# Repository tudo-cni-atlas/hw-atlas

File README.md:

hw-altas
================
## Firmware 

The firmware for STM32-based ATLAS anchor and tag nodes is provided as .elf file. 

## Hardware design
A minimal node PCB for the DecaWave DWM1000 module and the STM32F103C8T6 Evaluation Board known as "Blue Pill".

### Project schematic:

### BOM
| Identifier | Type/Value | Quantity | Supplier Id | Supplier | Comment |
| ---        | ---        | ---      | ---         | ---      | ---     |
| R1-R7 | 10 kΩ | 7 | RND 0805 1 1,0K | [Reichelt][reichelt] |
| C7 | 470 pF | 1 | NPO-G0805 470P | [Reichelt][reichelt] |
| C5, C6 | 10 µF | 2 | RND 1500805X1062 | [Reichelt][reichelt] |
| C1-C4 | 22 µF | 4 | X5R 0805 DB 22U | [Reichelt][reichelt] |
| LED_SYS | LED white | 1 | SLO SMD-W0805-0 | [Reichelt][reichelt] |
| LED_ERR | LED red | 1 | OSO LHR974 | [Reichelt][reichelt] |
| LED_SYS | LED white | 1 | SLO SMD-W0805-0 | [Reichelt][reichelt] |
| LED_TX | LED red | 1 | OSO LHR974 | [Reichelt][reichelt] |
| LED_RX | LED green | 1 | OSO LGR971 | [Reichelt][reichelt] |
| LED_SFD | LED yellow | 1 | RND 135-00051 | [Reichelt][reichelt] |
| LED_OK | LED green | 1 | OSO LGR971 | [Reichelt][reichelt] |
| IC1 | DWM1000 | 1 | 1479-1002-1-ND | [Digikey][digikey] |
| IC2 | MIC5219-3.3 | 1 | - | [Aliexpress][aliexpress] |
| BOARD1 | STM32 Eval Board | 1 | - | [Aliexpress][aliexpress] |

[reichelt]: http://www.reichelt.de
[mouser]: http://mouser.com
[aliexpress]: http://www.aliexpress.com
[digikey]: http://www.digikey.de

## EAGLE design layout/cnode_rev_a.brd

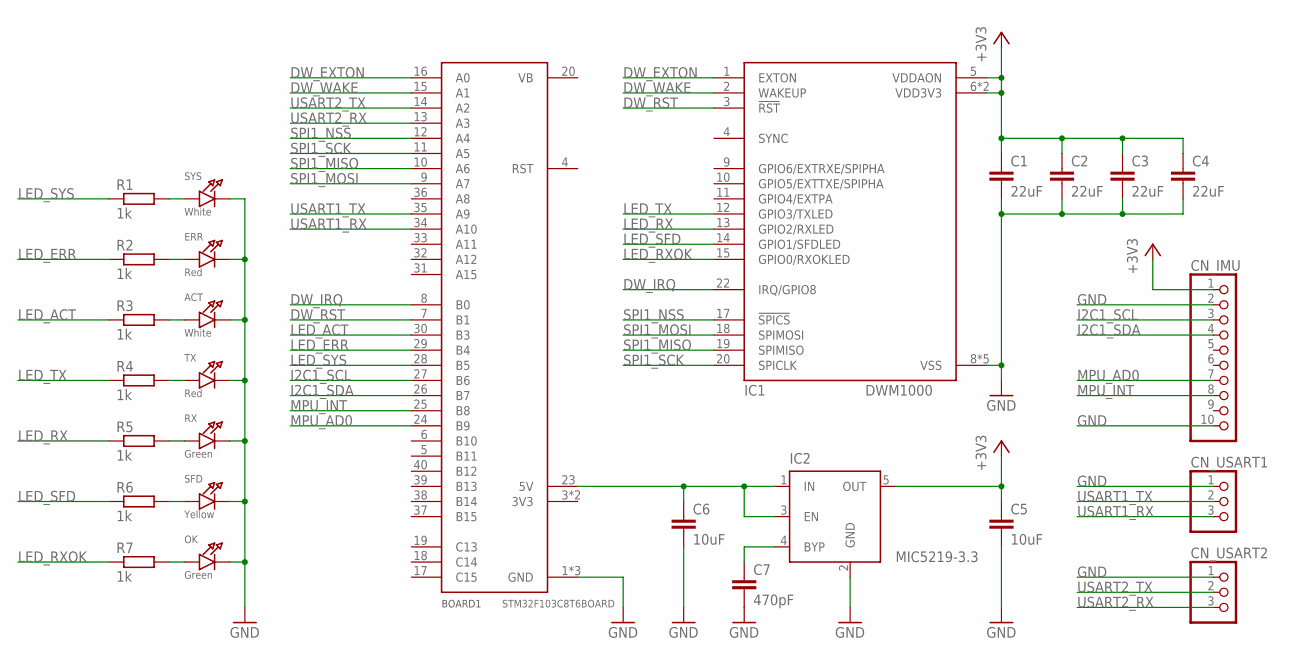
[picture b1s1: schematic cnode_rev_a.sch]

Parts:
ACT: White; CHIPLED_0805_NOOUTLINE
BOARD1: STM32F103C8T6BOARD
C1, C2, C3, C4: 22uF; C0805
C5, C6: 10uF; C0805
C7: 470pF; C0805
CN_IMU: HEADER-1X10ROUND; 1X10_ROUND
CN_USART1, CN_USART2: HEADER-1X3ROUND; 1X03_ROUND
ERR: Red; CHIPLED_0805_NOOUTLINE
IC1: DWM1000
IC2: MIC5219-3.3; SOT23-5
OK: Green; CHIPLED_0805_NOOUTLINE
R1, R2, R3, R4, R5, R6, R7: 1k; R0805
RX: Green; CHIPLED_0805_NOOUTLINE
SFD: Yellow; CHIPLED_0805_NOOUTLINE
SYS: White; CHIPLED_0805_NOOUTLINE
TX: Red; CHIPLED_0805_NOOUTLINE

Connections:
+3V3: C1.1, C2.1, C3.1, C4.1, C5.1, CN_IMU.1, IC1.5 (VDDAON), IC1.6 (VDD3V3), IC1.7 (VDD3V3), IC2.5 (OUT)
DW_EXTON: BOARD1.16 (A0), IC1.1 (EXTON)
DW_IRQ: BOARD1.8 (B0), IC1.22 (IRQ/GPIO8)
DW_RST: BOARD1.7 (B1), IC1.3 (!RST)
DW_WAKE: BOARD1.15 (A1), IC1.2 (WAKEUP)
GND: ACT.C, BOARD1.1 (GND), BOARD1.2 (GND), BOARD1.22 (GND), C1.2, C2.2, C3.2, C4.2, C5.2, C6.2, C7.2, CN_IMU.2, CN_IMU.10, CN_USART1.1, CN_USART2.1, ERR.C, IC1.8 (VSS), IC1.16 (VSS), IC1.21 (VSS), IC1.23 (VSS), IC1.24 (VSS), IC2.2 (GND), OK.C, RX.C, SFD.C, SYS.C, TX.C
I2C1_SCL: BOARD1.27 (B6), CN_IMU.3
I2C1_SDA: BOARD1.26 (B7), CN_IMU.4
LED_ACT: BOARD1.30 (B3), R3.1
LED_ERR: BOARD1.29 (B4), R2.1
LED_RX: IC1.13 (GPIO2/RXLED), R5.1
LED_RXOK: IC1.15 (GPIO0/RXOKLED), R7.1
LED_SFD: IC1.14 (GPIO1/SFDLED), R6.1
LED_SYS: BOARD1.28 (B5), R1.1
LED_TX: IC1.12 (GPIO3/TXLED), R4.1
MPU_AD0: BOARD1.24 (B9), CN_IMU.7
MPU_INT: BOARD1.25 (B8), CN_IMU.8
unnamed: R5.2, RX.A
unnamed: R4.2, TX.A
unnamed: ACT.A, R3.2
unnamed: ERR.A, R2.2
unnamed: R1.2, SYS.A
unnamed: BOARD1.23 (5V), C6.1, IC2.1 (IN), IC2.3 (EN)
unnamed: C7.1, IC2.4 (BYP)
unnamed: R6.2, SFD.A
unnamed: OK.A, R7.2
SPI1_MISO: BOARD1.10 (A6), IC1.19 (SPIMISO)
SPI1_MOSI: BOARD1.9 (A7), IC1.18 (SPIMOSI)
SPI1_NSS: BOARD1.12 (A4), IC1.17 (!SPICS)
SPI1_SCK: BOARD1.11 (A5), IC1.20 (SPICLK)
USART1_RX: BOARD1.34 (A10), CN_USART1.3
USART1_TX: BOARD1.35 (A9), CN_USART1.2
USART2_RX: BOARD1.13 (A3), CN_USART2.3
USART2_TX: BOARD1.14 (A2), CN_USART2.2

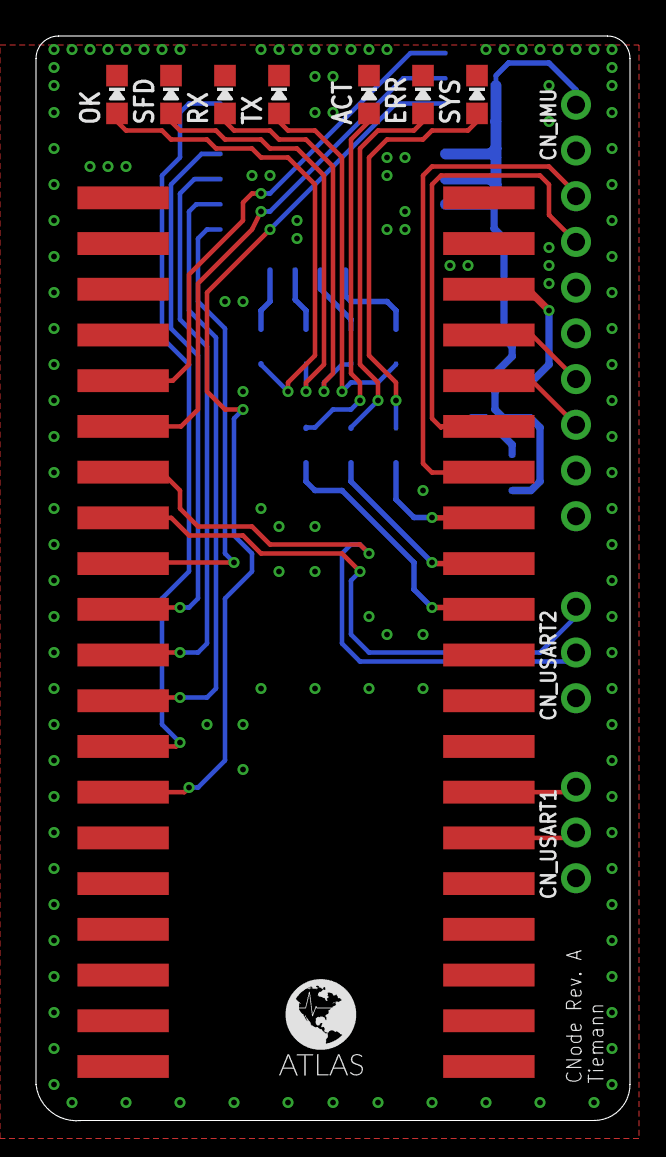
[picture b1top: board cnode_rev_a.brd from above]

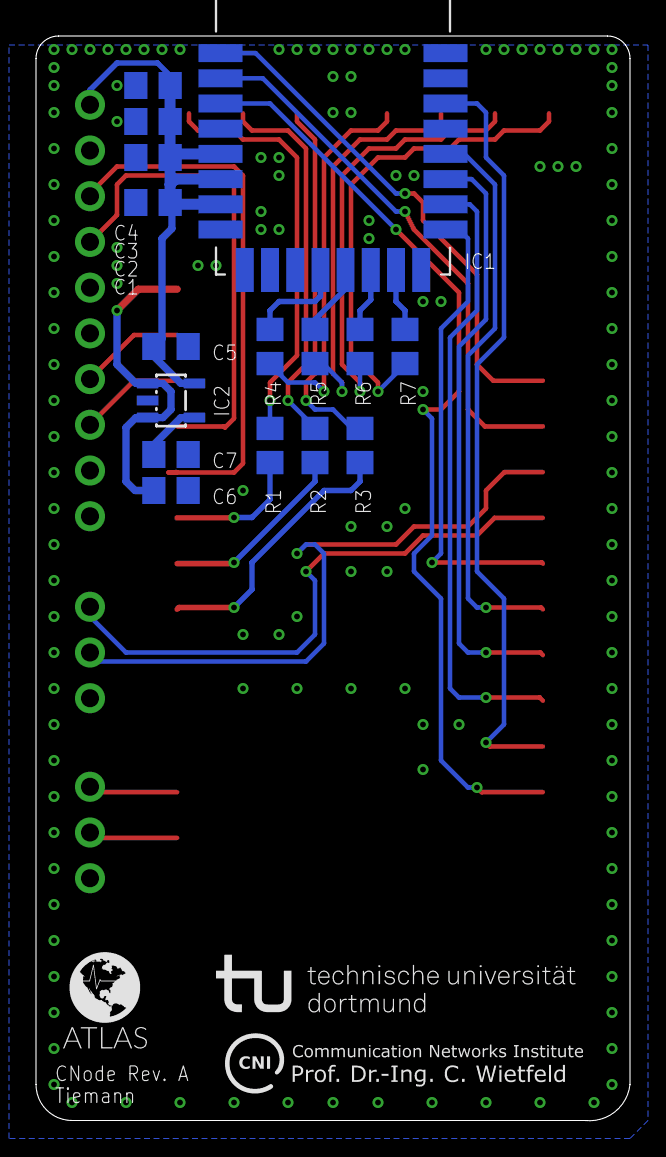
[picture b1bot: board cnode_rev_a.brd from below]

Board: 2 copper layers, 33.0 x 60.3 mm, 31 parts (19 on the bottom side), 34 nets.

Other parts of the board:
U$2, U$4: ATLAS_LOGO_5MM
U$5: CNI-BANNER-EN_20MM
U$6: TU-BANNER_20MM

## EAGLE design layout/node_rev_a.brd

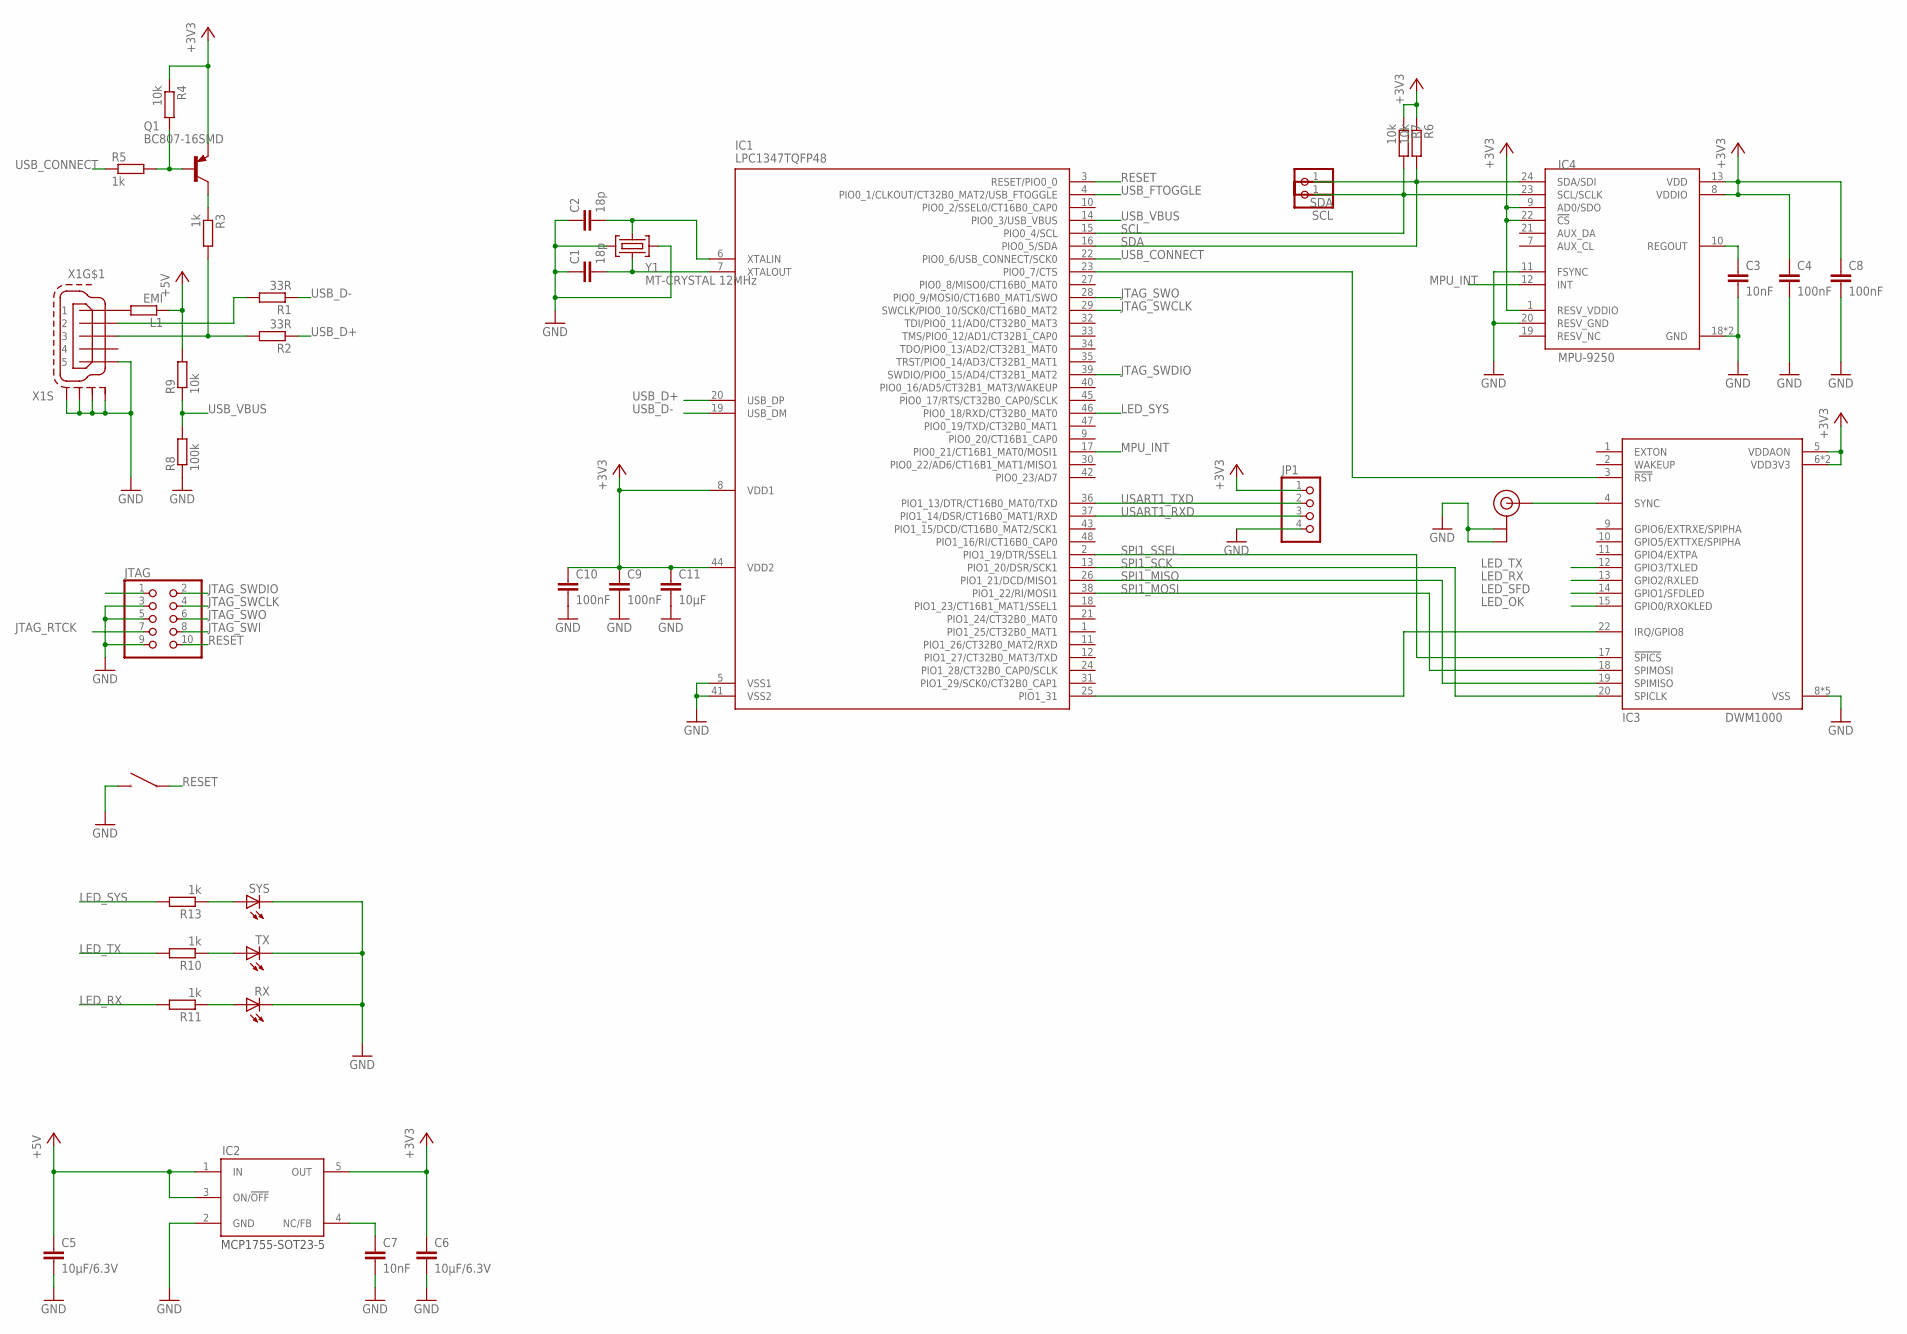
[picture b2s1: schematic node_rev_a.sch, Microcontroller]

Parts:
C1, C2: 18p; C0603
C3, C7: 10nF; C0603
C4, C8, C9, C10: 100nF; C0603
C5, C6: 10µF/6.3V; C0603
C11: 10µF; C0603
IC1: LPC1347TQFP48; LQFP48-7X7
IC2: MCP1755-SOT23-5; SOT23-5
IC3: DWM1000
IC4: MPU-9250; QFN24_3MM
JP1: HEADER-1X4ROUND; 1X04_ROUND
JTAG: ARM-JTAG_1.27-SMD; 20021121-10010XXLF
L1: EMI; R0603
Q1: BC807-16SMD; SOT23-BEC
R1, R2: 33R; R0603
R3, R5, R10, R11, R13: 1k; R0603
R4, R6, R7, R9: 10k; R0603
R8: 100k; R0603
RX: LEDCHIP-LED0603; CHIP-LED0603
SCL: HEADER-1X12MM; 1X01_2MM
SDA: HEADER-1X12MM; 1X01_2MM
SYNC: U.FL
SYS: LEDCHIP-LED0603; CHIP-LED0603
TX: LEDCHIP-LED0603; CHIP-LED0603
U$1: TACT-SWITCH-40-40; 40-40
X1: MINI-USB-SCHIELD-32005-201; 32005-201
Y1: MT-CRYSTAL 12MHz; MT

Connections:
+3V3: C4.1, C6.1, C8.1, C9.1, C10.1, C11.1, IC1.8 (VDD1), IC1.44 (VDD2), IC2.5 (OUT), IC3.5 (VDDAON), IC3.6 (VDD3V3), IC3.7 (VDD3V3), IC4.1 (RESV_VDDIO), IC4.8 (VDDIO), IC4.9 (AD0/SDO), IC4.13 (VDD), IC4.22 (!CS), JP1.1, Q1.E, R4.1, R6.1, R7.1
+5V: C5.1, IC2.1 (IN), IC2.3 (ON/!OFF), L1.1, R9.2
GND: C1.1, C2.1, C3.2, C4.2, C5.2, C6.2, C7.2, C8.2, C9.2, C10.2, C11.2, IC1.5 (VSS1), IC1.41 (VSS2), IC2.2 (GND), IC3.8 (VSS), IC3.16 (VSS), IC3.21 (VSS), IC3.23 (VSS), IC3.24 (VSS), IC4.11 (FSYNC), IC4.18 (GND), IC4.20 (RESV_GND), IC4.THERM (GND), JP1.4, JTAG.3, JTAG.5, JTAG.9, R8.1, RX.C, SYNC.1 (GND), SYNC.2 (GND), SYS.C, TX.C, U$1.1, U$1.2, X1.5, X1.M1 (S1), X1.M2 (S2), X1.M3 (S3), X1.M4 (S4), Y1.2 (GND2), Y1.4 (GND1)
JTAG_RTCK: JTAG.7
JTAG_SWCLK: IC1.29 (SWCLK/PIO0_10/SCK0/CT16B0_MAT2), JTAG.4
JTAG_SWDIO: IC1.39 (SWDIO/PIO0_15/AD4/CT32B1_MAT2), JTAG.2
JTAG_SWI: JTAG.8
JTAG_SWO: IC1.28 (PIO0_9/MOSI0/CT16B0_MAT1/SWO), JTAG.6
LED_OK: IC3.15 (GPIO0/RXOKLED)
LED_RX: IC3.13 (GPIO2/RXLED), R11.2
LED_SFD: IC3.14 (GPIO1/SFDLED)
LED_SYS: IC1.46 (PIO0_18/RXD/CT32B0_MAT0), R13.2
LED_TX: IC3.12 (GPIO3/TXLED), R10.2
MPU_INT: IC1.17 (PIO0_21/CT16B1_MAT0/MOSI1), IC4.12 (INT)
unnamed: Q1.B, R4.2, R5.2
unnamed: Q1.C, R3.1
unnamed: L1.2, X1.1
unnamed: IC1.25 (PIO1_31), IC3.22 (IRQ/GPIO8)
unnamed: R1.2, X1.2
unnamed: IC3.4 (SYNC), SYNC.3 (SIGNAL)
unnamed: IC1.23 (PIO0_7/CTS), IC3.3 (!RST)
unnamed: R10.1, TX.A
unnamed: R11.1, RX.A
unnamed: R13.1, SYS.A
unnamed: C3.1, IC4.10 (REGOUT)
unnamed: C7.1, IC2.4 (NC/FB)
unnamed: R2.2, R3.2, X1.3
RESET: IC1.3 (RESET/PIO0_0), JTAG.10, U$1.3, U$1.4
SCL: IC1.15 (PIO0_4/SCL), IC4.23 (SCL/SCLK), R7.2, SCL.1
SDA: IC1.16 (PIO0_5/SDA), IC4.24 (SDA/SDI), R6.2, SDA.1
SPI1_MISO: IC1.26 (PIO1_21/DCD/MISO1), IC3.19 (SPIMISO)
SPI1_MOSI: IC1.38 (PIO1_22/RI/MOSI1), IC3.18 (SPIMOSI)
SPI1_SCK: IC1.13 (PIO1_20/DSR/SCK1), IC3.20 (SPICLK)
SPI1_SSEL: IC1.2 (PIO1_19/DTR/SSEL1), IC3.17 (!SPICS)
USART1_RXD: IC1.37 (PIO1_14/DSR/CT16B0_MAT1/RXD), JP1.3
USART1_TXD: IC1.36 (PIO1_13/DTR/CT16B0_MAT0/TXD), JP1.2
USB_CONNECT: IC1.22 (PIO0_6/USB_CONNECT/SCK0), R5.1
USB_D+: IC1.20 (USB_DP), R2.1
USB_D-: IC1.19 (USB_DM), R1.1
USB_FTOGGLE: IC1.4 (PIO0_1/CLKOUT/CT32B0_MAT2/USB_FTOGGLE)
USB_VBUS: IC1.14 (PIO0_3/USB_VBUS), R8.2, R9.1
XTAL1: C2.2, IC1.6 (XTALIN), Y1.1 (CRYSTAL2)
XTAL2: C1.2, IC1.7 (XTALOUT), Y1.3 (CRYSTAL1)

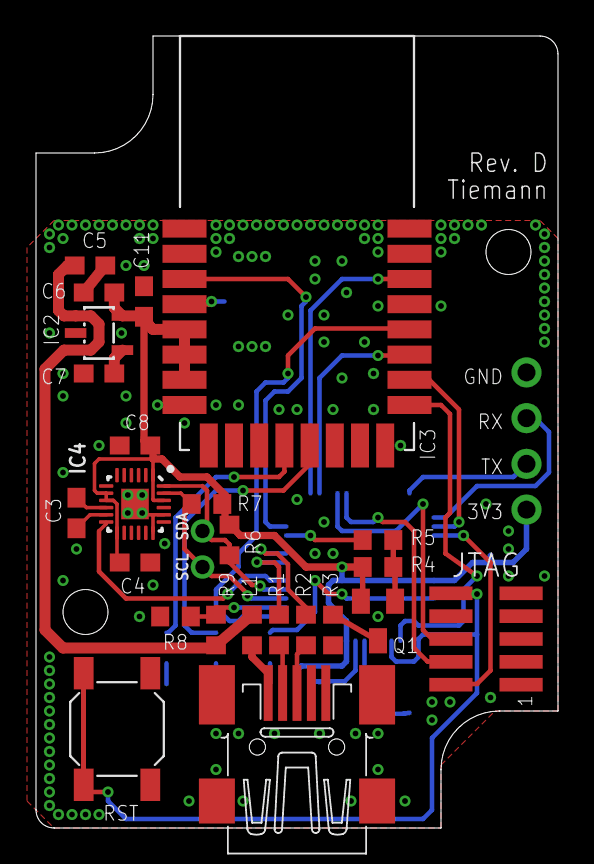
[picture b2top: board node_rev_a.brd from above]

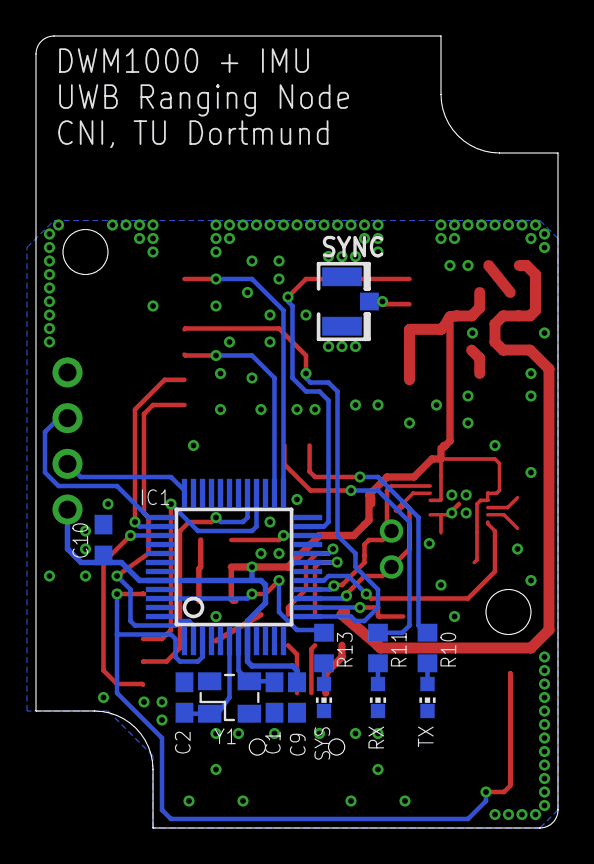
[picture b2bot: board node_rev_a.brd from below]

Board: 2 copper layers, 29.0 x 44.0 mm, 40 parts (13 on the bottom side), 38 nets.

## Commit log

2018-09-06 Updated to STM32-based node for ATLAS 2.0 release
2018-09-06 Added picture of assembled board
2018-09-06 Resized image
2018-09-15 Minor changes in readme to account for render width
2018-09-15 Added zenodo badge
2021-05-26 added fw

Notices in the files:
parts and their libraries:
microbuilder: This work is placed in the public domain, and may be freely used for commercial and non-commercial work with the following conditions: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
